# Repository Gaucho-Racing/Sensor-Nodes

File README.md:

# Sensor Node hardware and software for GR25

---

## Hardware 
The Hardware is split into a couple of folders and have Kicad projects that relate to the Sensor Nodes. This includes random projects and some hardware that might have been usefull.

---

## Software

Includes software for the Sensor Nodes

### Compilation:

To compile and be able to debug the project you need the following: 
- CMAKE 
- arm-none-eabi-gcc
- openocd
- ninja
- VSCode CMAKE extension
- VSCode Cortex Debug extension

**Make sure cmake, arm tolchian, openocd,and ninja are added to path**

To check the version run: 
- cmake --version
- arm-none-eabi-gcc --version
- openocd --version
- ninja --version

After everything is installed you should be able to follow the VSCode UI to compile and debug.

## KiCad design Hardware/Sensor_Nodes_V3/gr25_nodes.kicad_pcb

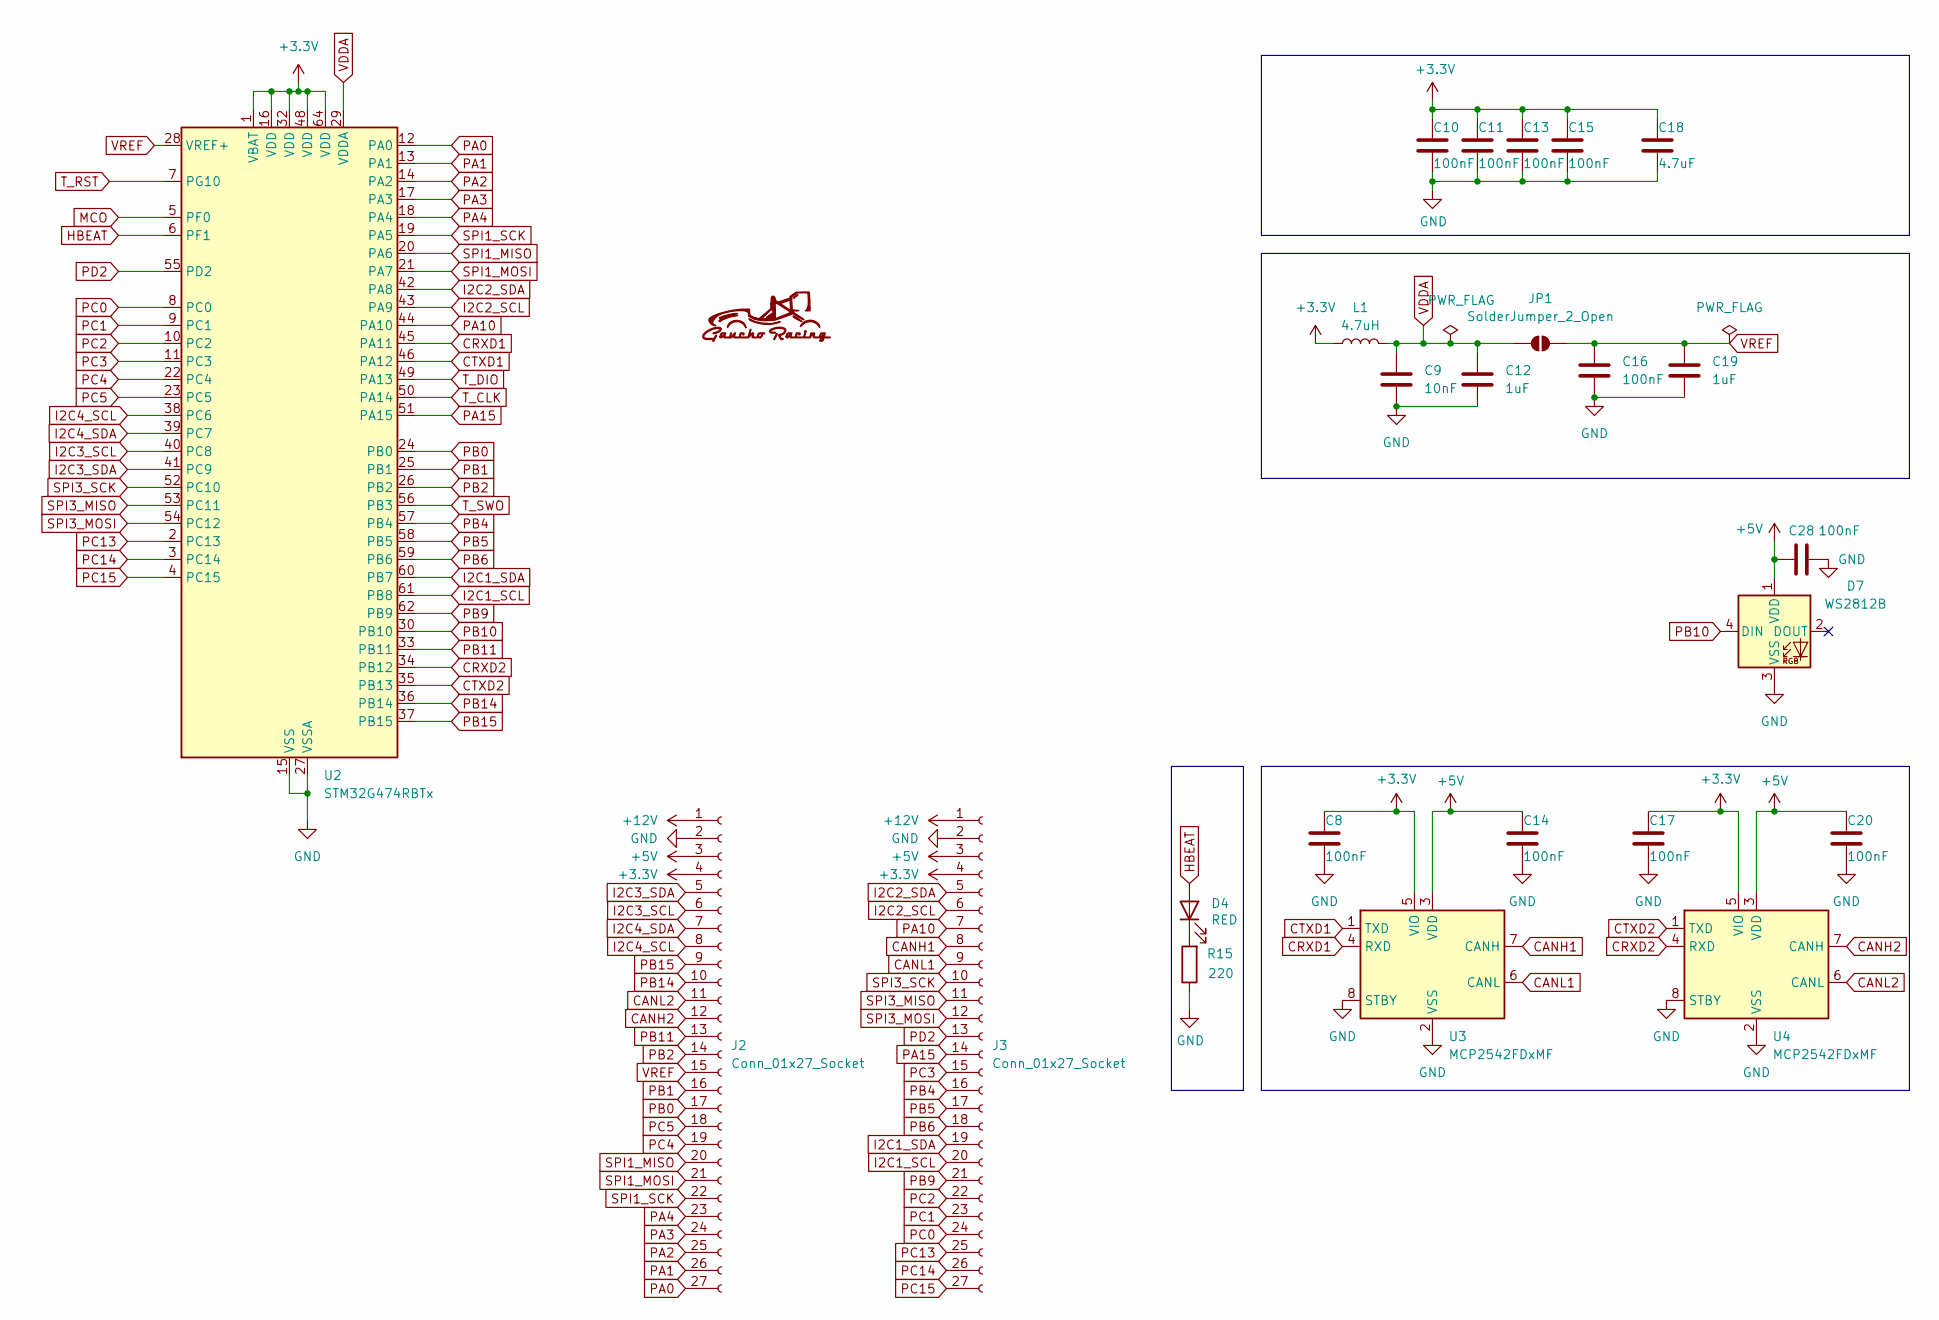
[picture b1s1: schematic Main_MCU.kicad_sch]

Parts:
C8, C10, C11, C13, C14, C15, C16, C17, C20: 100nF; C_0603_1608Metric; LCSC C14663
C9: 10nF; C_0603_1608Metric; LCSC C57112
C12, C19: 1uF; C_0603_1608Metric; LCSC C15849
C18: 4.7uF; C_0603_1608Metric; LCSC C19666
C28: 100nF; C_0603_1608Metric
D4: RED; LED_0603_1608Metric; LCSC C2286
D7: WS2812B; LED_WS2812B_PLCC4_5.0x5.0mm_P3.2mm
J2, J3: Conn_01x27_Socket; PinHeader_1x27_P2.54mm_Vertical
JP1: SolderJumper_2_Open; SolderJumper-2_P1.3mm_Open_TrianglePad1.0x1.5mm
L1: 4.7uH; C_1206_3216Metric; LCSC C1049
R15: 220; R_0402_1005Metric; LCSC C25091
U2: STM32G474RBTx; LQFP-64_10x10mm_P0.5mm; LCSC C529413
U3, U4: MCP2542FDxMF; SOIC-8_3.9x4.9mm_P1.27mm

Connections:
+3.3V: C8.1, C10.1, C11.1, C13.1, C15.1, C17.1, C18.1, J2.4, J3.4, L1.1, U2.1 (VBAT), U2.16 (VDD), U2.32 (VDD), U2.48 (VDD), U2.64 (VDD), U3.5 (VIO), U4.5 (VIO); also elsewhere on the board
+5V: C14.1, C20.1, C28.2, D7.1 (VDD), J2.3, J3.3, U3.3 (VDD), U4.3 (VDD); also elsewhere on the board
+12V: J2.1, J3.1; also elsewhere on the board
CANH1: J3.8, U3.7 (CANH)
CANH2: J2.12, U4.7 (CANH)
CANL1: J3.9, U3.6 (CANL)
CANL2: J2.11, U4.6 (CANL)
CRXD1: U2.45 (PA11), U3.4 (RXD)
CRXD2: U2.34 (PB12), U4.4 (RXD)
CTXD1: U2.46 (PA12), U3.1 (TXD)
CTXD2: U2.35 (PB13), U4.1 (TXD)
GND: C8.2, C9.2, C10.2, C11.2, C12.2, C13.2, C14.2, C15.2, C16.2, C17.2, C18.2, C19.2, C20.2, C28.1, D7.3 (VSS), J2.2, J3.2, R15.1, U2.15 (VSS), U2.27 (VSSA), U2.31 (VSS), U2.47 (VSS), U2.63 (VSS), U3.2 (VSS), U3.8 (STBY), U3.9 (VSS), U4.2 (VSS), U4.8 (STBY), U4.9 (VSS); also elsewhere on the board
HBEAT: D4.2 (A), U2.6 (PF1)
I2C1_SCL: J3.20, U2.61 (PB8)
I2C1_SDA: J3.19, U2.60 (PB7)
I2C2_SCL: J3.6, U2.43 (PA9)
I2C2_SDA: J3.5, U2.42 (PA8)
I2C3_SCL: J2.6, U2.40 (PC8)
I2C3_SDA: J2.5, U2.41 (PC9)
I2C4_SCL: J2.8, U2.38 (PC6)
I2C4_SDA: J2.7, U2.39 (PC7)
MCO: U2.5 (PF0); also elsewhere on the board
unnamed: D4.1 (K), R15.2
PA0: J2.27, U2.12 (PA0)
PA1: J2.26, U2.13 (PA1)
PA2: J2.25, U2.14 (PA2)
PA3: J2.24, U2.17 (PA3)
PA4: J2.23, U2.18 (PA4)
PA10: J3.7, U2.44 (PA10)
PA15: J3.14, U2.51 (PA15)
PB0: J2.17, U2.24 (PB0)
PB1: J2.16, U2.25 (PB1)
PB2: J2.14, U2.26 (PB2)
PB4: J3.16, U2.57 (PB4)
PB5: J3.17, U2.58 (PB5)
PB6: J3.18, U2.59 (PB6)
PB9: J3.21, U2.62 (PB9)
PB10: D7.4 (DIN), U2.30 (PB10)
PB11: J2.13, U2.33 (PB11)
PB14: J2.10, U2.36 (PB14)
PB15: J2.9, U2.37 (PB15)
PC0: J3.24, U2.8 (PC0)
PC1: J3.23, U2.9 (PC1)
PC2: J3.22, U2.10 (PC2)
PC3: J3.15, U2.11 (PC3)
PC4: J2.19, U2.22 (PC4)
PC5: J2.18, U2.23 (PC5)
PC13: J3.25, U2.2 (PC13)
PC14: J3.26, U2.3 (PC14)
PC15: J3.27, U2.4 (PC15)
PD2: J3.13, U2.55 (PD2)
SPI1_MISO: J2.20, U2.20 (PA6)
SPI1_MOSI: J2.21, U2.21 (PA7)
SPI1_SCK: J2.22, U2.19 (PA5)
SPI3_MISO: J3.11, U2.53 (PC11)
SPI3_MOSI: J3.12, U2.54 (PC12)
SPI3_SCK: J3.10, U2.52 (PC10)
T_CLK: U2.50 (PA14); also elsewhere on the board
T_DIO: U2.49 (PA13); also elsewhere on the board
T_RST: U2.7 (PG10); also elsewhere on the board
T_SWO: U2.56 (PB3); also elsewhere on the board
VDDA: C9.1, C12.1, JP1.1 (A), L1.2, U2.29 (VDDA)
VREF: C16.1, C19.1, J2.15, JP1.2 (B), U2.28 (VREF+)

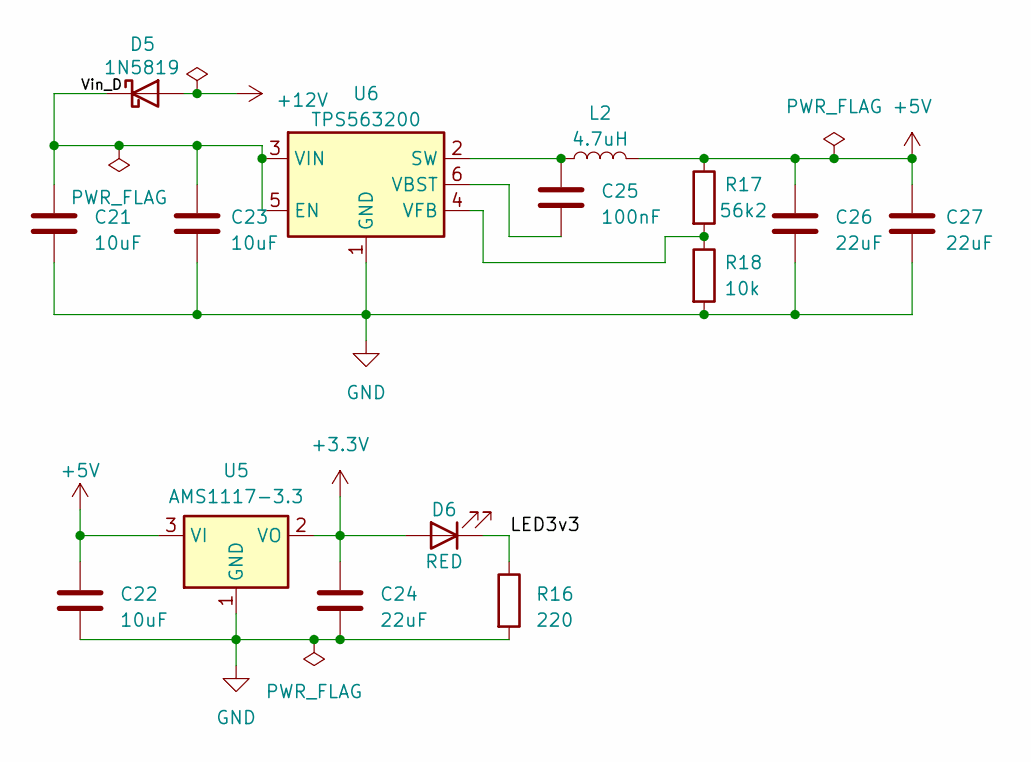
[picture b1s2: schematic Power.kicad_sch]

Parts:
C21, C22, C23: 10uF; C_0805_2012Metric; LCSC C15850
C24, C26, C27: 22uF; C_0805_2012Metric; LCSC C45783
C25: 100nF; C_0603_1608Metric; LCSC C14663
D5: 1N5819; D_SOD-323_HandSoldering; LCSC C191023
D6: RED; LED_0603_1608Metric; LCSC C2286
L2: 4.7uH; L_Cenker_CKCS6020; LCSC C5291878
R16: 220; R_0402_1005Metric; LCSC C25091
R17: 56k2; R_0402_1005Metric; LCSC C25796
R18: 10k; R_0402_1005Metric; LCSC C25744
U5: AMS1117-3.3; SOT-223-3_TabPin2; LCSC C6186
U6: TPS563200; SOT-23-6; LCSC C97253

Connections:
+3.3V: C24.1, D6.2 (A), U5.2 (VO); also elsewhere on the board
+5V: C22.1, C26.1, C27.1, L2.2, R17.1, U5.3 (VI); also elsewhere on the board
+12V: D5.2 (A); also elsewhere on the board
/Power/LED3v3: D6.1 (K), R16.1
/Power/Vin_D: C21.1, C23.1, D5.1 (K), U6.3 (VIN), U6.5 (EN)
GND: C21.2, C22.2, C23.2, C24.2, C26.2, C27.2, R16.2, R18.2, U5.1 (GND), U6.1 (GND); also elsewhere on the board
unnamed: C25.1, L2.1, U6.2 (SW)
unnamed: C25.2, U6.6 (VBST)
unnamed: R17.2, R18.1, U6.4 (VFB)

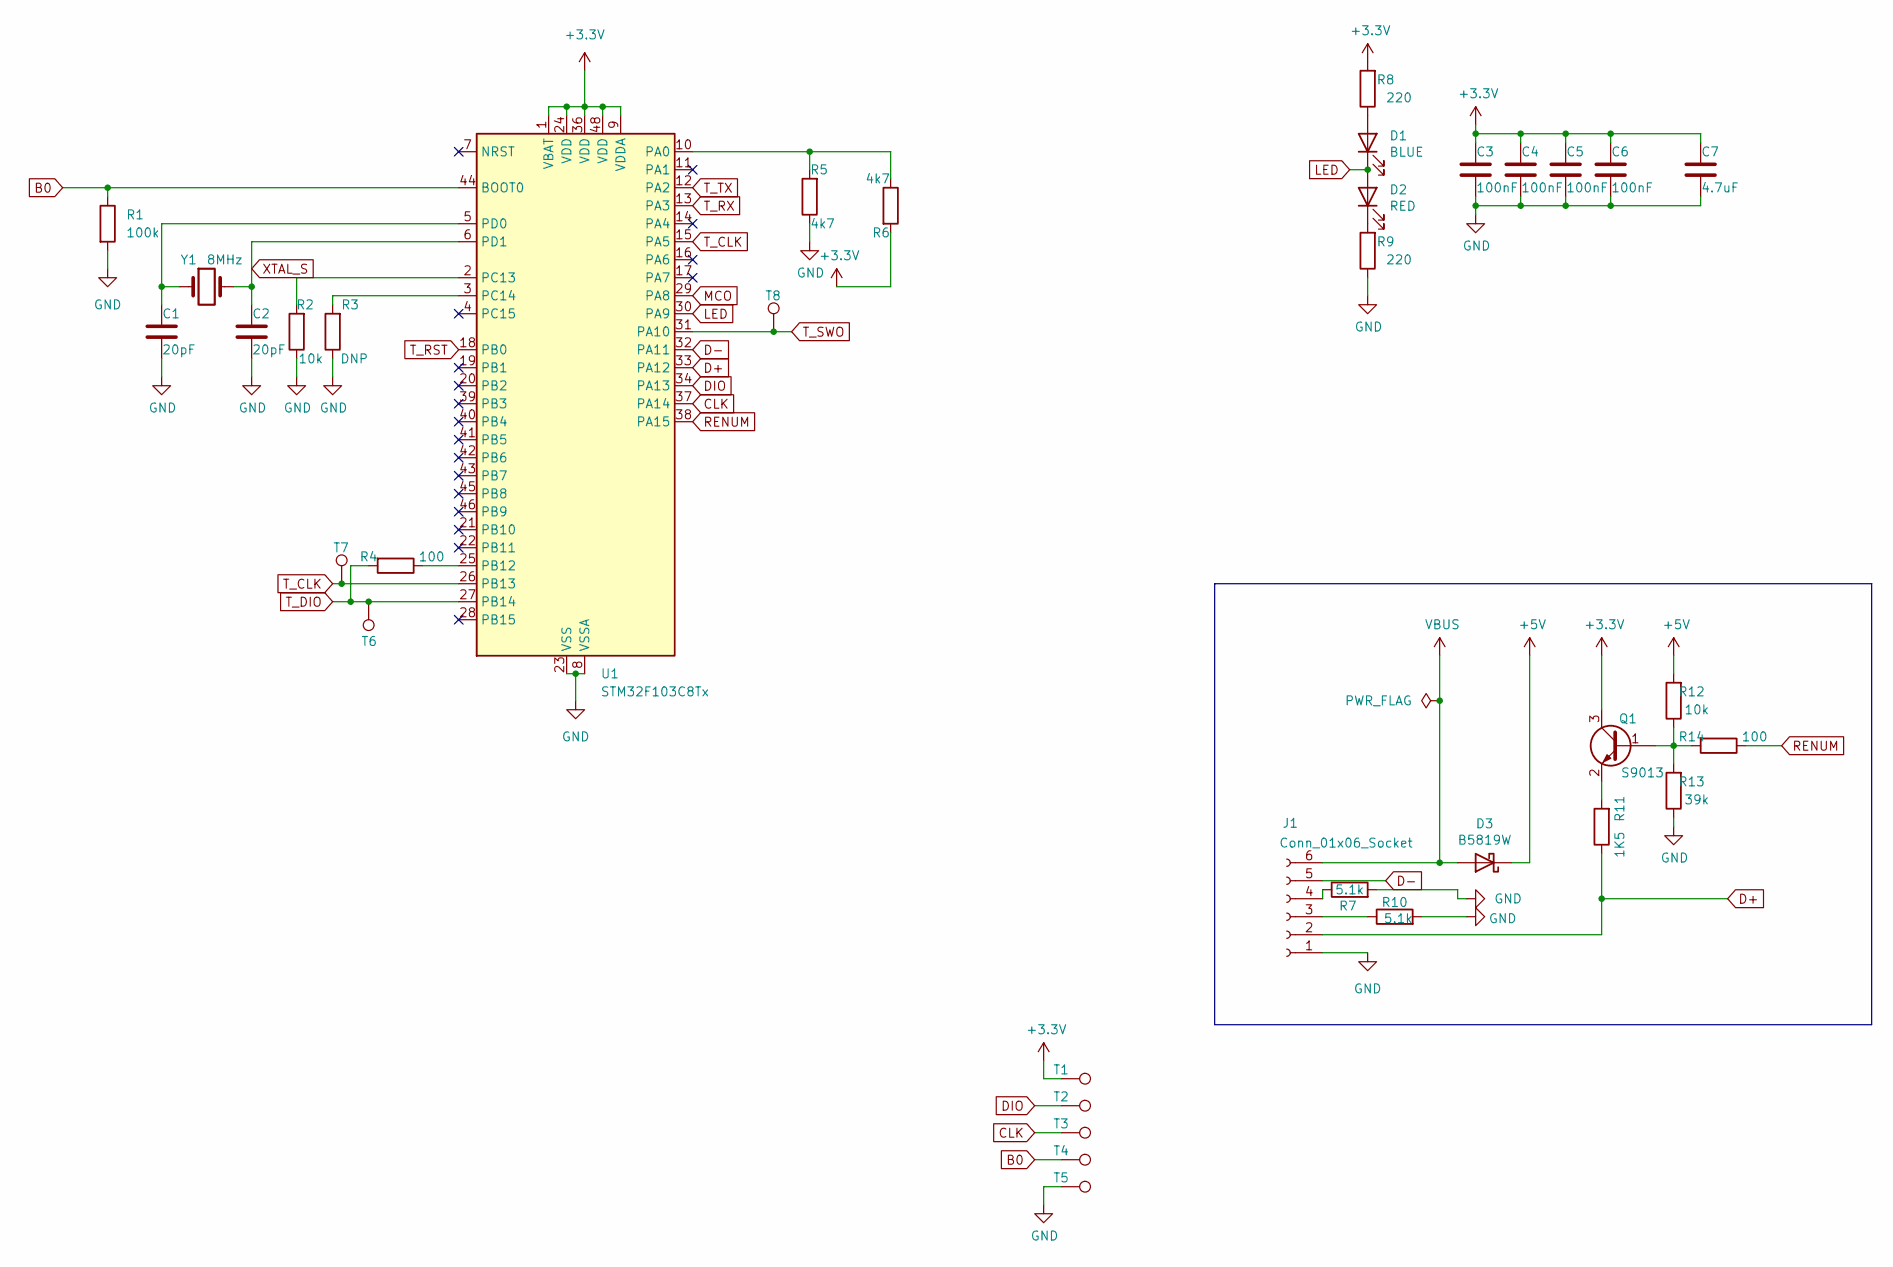
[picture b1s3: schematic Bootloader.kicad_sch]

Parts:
C1, C2: 20pF; C_0603_1608Metric; LCSC C1648
C3, C4, C5, C6: 100nF; C_0603_1608Metric; LCSC C14663
C7: 4.7uF; C_0603_1608Metric; LCSC C19666
D1: BLUE; LED_0603_1608Metric; LCSC C2290
D2: RED; LED_0603_1608Metric; LCSC C2286
D3: B5819W; D_SOD-123; LCSC C8598
J1: Conn_01x06_Socket; JST_PH_B6B-PH-K_1x06_P2.00mm_Vertical
Q1: S9013; SOT-23; LCSC C6749
R1: 100k; R_0402_1005Metric; LCSC C25741
R2, R12: 10k; R_0402_1005Metric; LCSC C25744
R3: DNP; R_0402_1005Metric; LCSC xxC25744
R4: 100; R_0603_1608Metric; LCSC C22775
R5, R6: 4k7; R_0402_1005Metric; LCSC C25900
R7, R10: 5.1k; R_0402_1005Metric; LCSC C25905
R8, R9: 220; R_0402_1005Metric; LCSC C25091
R11: 1K5; R_0402_1005Metric; LCSC C25867
R13: 39k; R_0402_1005Metric; LCSC C25783
R14: 100; R_0402_1005Metric; LCSC C25076
T1, T2, T3, T4, T5, T6, T7, T8: TestPoint_Pad_1.0x1.0mm
U1: STM32F103C8Tx; LQFP-48_7x7mm_P0.5mm; LCSC C8734
Y1: 8MHz; Crystal_SMD_5032-2Pin_5.0x3.2mm; LCSC C115962

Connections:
+3.3V: C3.1, C4.1, C5.1, C6.1, C7.1, Q1.3 (C), R6.2, R8.2, T1.1, U1.1 (VBAT), U1.9 (VDDA), U1.24 (VDD), U1.36 (VDD), U1.48 (VDD); also elsewhere on the board
+5V: D3.1 (K), R12.2; also elsewhere on the board
B0: R1.1, T4.1, U1.44 (BOOT0)
CLK: T3.1, U1.37 (PA14)
D+: J1.2, R11.1, U1.33 (PA12)
D-: J1.5, U1.32 (PA11)
DIO: T2.1, U1.34 (PA13)
GND: C1.2, C2.2, C3.2, C4.2, C5.2, C6.2, C7.2, J1.1, R1.2, R2.1, R3.1, R5.1, R7.2, R9.1, R10.2, R13.1, T5.1, U1.8 (VSSA), U1.23 (VSS), U1.35 (VSS), U1.47 (VSS); also elsewhere on the board
LED: D1.1 (K), D2.2 (A), U1.30 (PA9)
MCO: U1.29 (PA8); also elsewhere on the board
unnamed: D1.2 (A), R8.1
unnamed: D2.1 (K), R9.2
unnamed: J1.3, R10.1
unnamed: J1.4, R7.1
unnamed: Q1.1 (B), R12.1, R13.2, R14.2
unnamed: Q1.2 (E), R11.2
unnamed: R5.2, R6.1, U1.10 (PA0)
unnamed: R4.1, U1.25 (PB12)
unnamed: R2.2, U1.2 (PC13)
unnamed: R3.2, U1.3 (PC14)
unnamed: C1.1, U1.5 (PD0), Y1.1
RENUM: R14.1, U1.38 (PA15)
T_CLK: T7.1, U1.15 (PA5), U1.26 (PB13); also elsewhere on the board
T_DIO: R4.2, T6.1, U1.27 (PB14); also elsewhere on the board
T_RST: U1.18 (PB0); also elsewhere on the board
T_RX: U1.13 (PA3)
T_SWO: T8.1, U1.31 (PA10); also elsewhere on the board
T_TX: U1.12 (PA2)
VBUS: D3.2 (A), J1.6
XTAL_S: C2.1, U1.6 (PD1), Y1.2

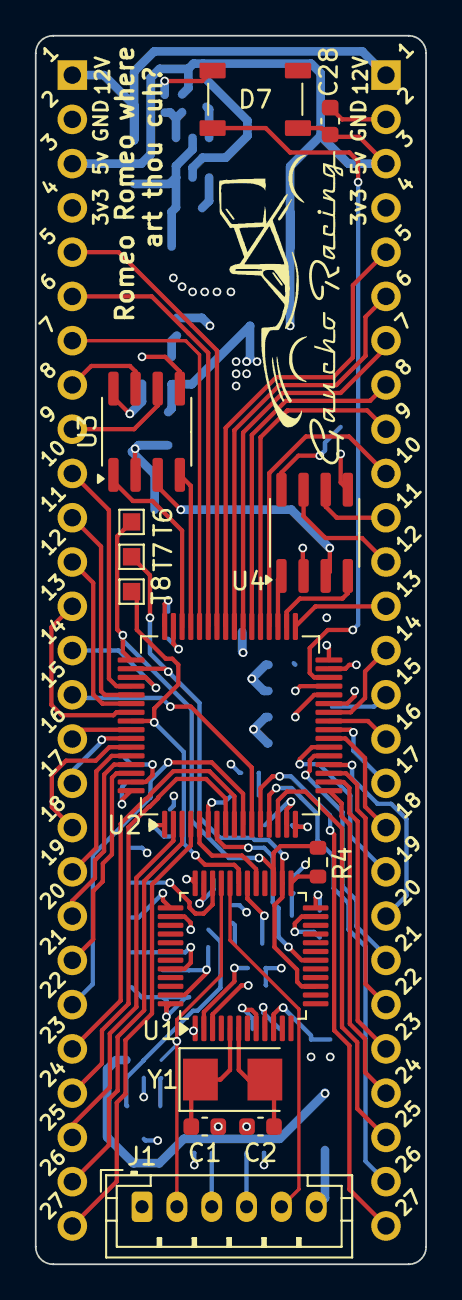
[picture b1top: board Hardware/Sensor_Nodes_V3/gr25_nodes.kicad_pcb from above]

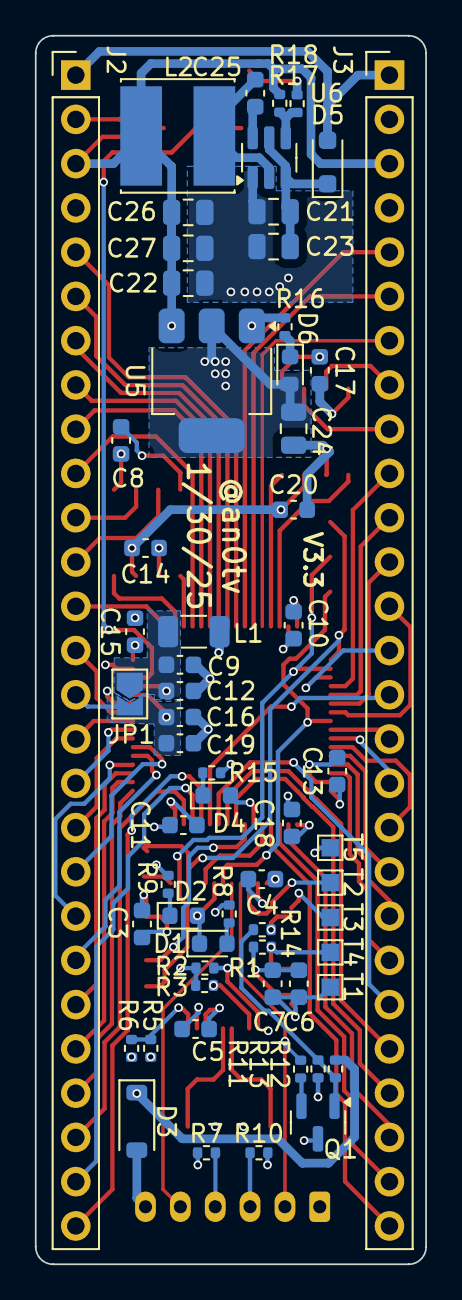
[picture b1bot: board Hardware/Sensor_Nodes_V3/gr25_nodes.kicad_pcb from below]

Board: 4 copper layers, 22.4 x 70.5 mm, 75 parts (61 on the bottom side), 88 nets.

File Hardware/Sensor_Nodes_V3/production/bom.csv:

Designator,Footprint,Quantity,Value,LCSC Part #
"_2, ",,2,,
"C1, C2",0603,2,20pF,C1648
"C10, C11, C13, C14, C15, C16, C17, C20, C25, C3, C4, C5, C6, C8",0603,14,100nF,C14663
"C12, C19",0603,2,1uF,C15849
"C18, C7",0603,2,4.7uF,C19666
"C21, C22, C23",0805,3,10uF, C15850
"C24, C26, C27",0805,3,22uF,C45783
C9,0603,1,10nF,C57112
D1,0603,1,BLUE, C2290
"D2, D4, D6",0603,3,RED,C2286
D3,D_SOD-123,1,B5819W,C8598
D5,D_SOD-323_HandSoldering,1,1N5819,C191023
J1,JST_PH_B6B-PH-K_1x06_P2.00mm_Vertical,1,Conn_01x06_Socket,
"J2, J3",PinHeader_1x27_P2.54mm_Vertical,2,Conn_01x27_Socket,
"KiKit_FID_B_1, KiKit_FID_B_2, KiKit_FID_B_3, KiKit_FID_T_1, KiKit_FID_T_2, KiKit_FID_T_3",Fiducial,6,Fiducial,
"KiKit_MB_1_1, KiKit_MB_1_2, KiKit_MB_1_3, KiKit_MB_1_4, KiKit_MB_1_5, KiKit_MB_2_1, KiKit_MB_2_2, KiKit_MB_2_3, KiKit_MB_2_4, KiKit_MB_2_5, KiKit_MB_3_1, KiKit_MB_3_2, KiKit_MB_3_3, KiKit_MB_3_4, KiKit_MB_3_5, KiKit_MB_4_1, KiKit_MB_4_2, KiKit_MB_4_3, KiKit_MB_4_4, KiKit_MB_4_5, KiKit_TO_1",NPTH,21,NPTH,
L1,1206,1,4.7uH,C1049
L2,L_Cenker_CKCS6020,1,4.7uH,C5291878
Q1,SOT-23,1,S9013,C6749
R1,0402,1,100k,C25741
"R10, R7",0402,2,5.1k,C25905
R11,0402,1,1K5,C25867
"R12, R18, R2",0402,3,10k,C25744
R13,0402,1,39k,C25783
R14,0402,1,100,C25076
"R15, R16, R8, R9",0402,4,220,C25091
R17,0402,1,56k2,C25796
R4,0603,1,100,C22775
"R5, R6",0402,2,4k7,C25900
"T1, T2, T3, T4, T5, T6, T7, T8",TestPoint_Pad_1.0x1.0mm,8,~,
U1,LQFP-48_7x7mm_P0.5mm,1,STM32F103C8Tx,C8734
U2,LQFP-64_10x10mm_P0.5mm,1,STM32G474RBTx,C529413
"U3, U4",SOIC-8_3.9x4.9mm_P1.27mm,2,MCP2542FDxMF,
U5,SOT-223-3_TabPin2,1,AMS1117-3.3,C6186
U6,SOT-23-6,1,TPS563200,C97253
Y1,Crystal_SMD_5032-2Pin_5.0x3.2mm,1,8MHz,C115962

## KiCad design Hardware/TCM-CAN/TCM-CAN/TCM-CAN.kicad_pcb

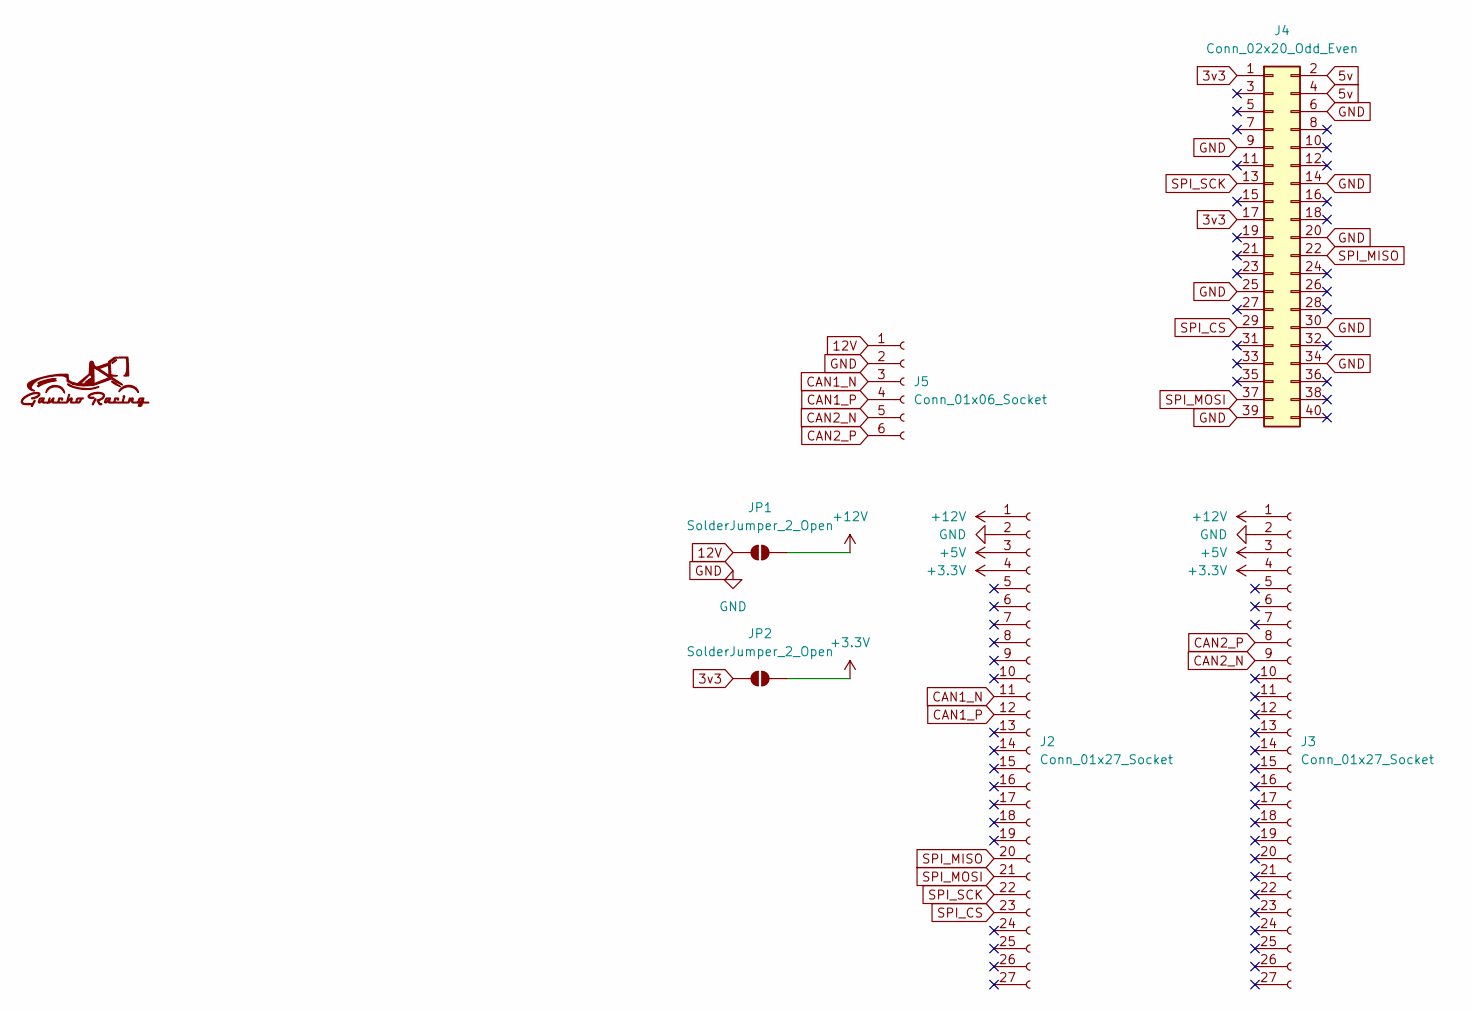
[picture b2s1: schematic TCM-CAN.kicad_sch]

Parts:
J2, J3: Conn_01x27_Socket; PinHeader_1x27_P2.54mm_Vertical
J4: Conn_02x20_Odd_Even; PinSocket_2x20_P2.54mm_Vertical
J5: Conn_01x06_Socket; JST_XH_B6B-XH-A_1x06_P2.50mm_Vertical
JP1, JP2: SolderJumper_2_Open; SolderJumper-2_P1.3mm_Open_Pad1.0x1.5mm

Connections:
3v3: J4.1, J4.17, JP2.1 (A)
5v: J4.2, J4.4
12V: J5.1, JP1.1 (A)
+3.3V: J2.4, J3.4, JP2.2 (B)
+5V: J2.3, J3.3
+12V: J2.1, J3.1, JP1.2 (B)
CAN1_N: J2.11, J5.3
CAN1_P: J2.12, J5.4
CAN2_N: J3.9, J5.5
CAN2_P: J3.8, J5.6
GND: J2.2, J3.2, J4.6, J4.9, J4.14, J4.20, J4.25, J4.30, J4.34, J4.39, J5.2
SPI_CS: J2.23, J4.29
SPI_MISO: J2.20, J4.22
SPI_MOSI: J2.21, J4.37
SPI_SCK: J2.22, J4.13

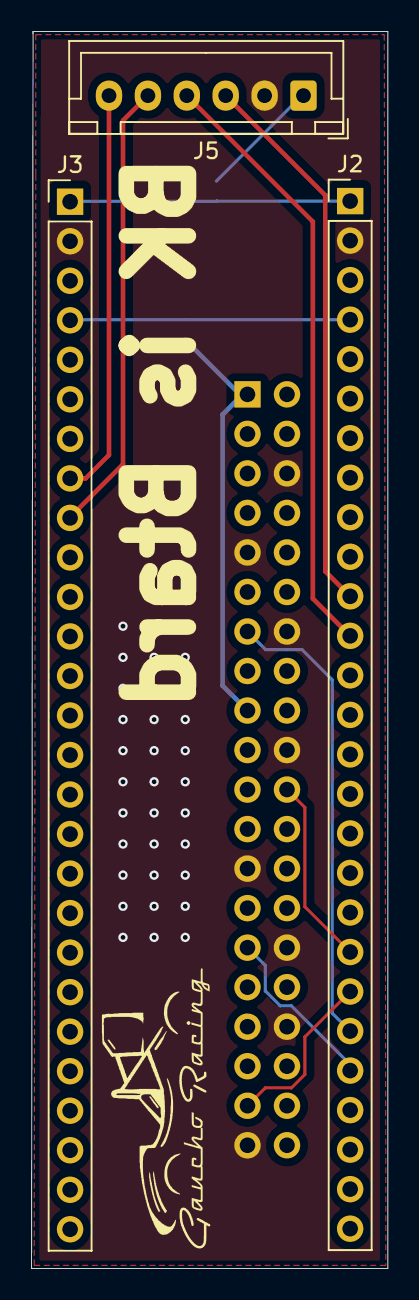
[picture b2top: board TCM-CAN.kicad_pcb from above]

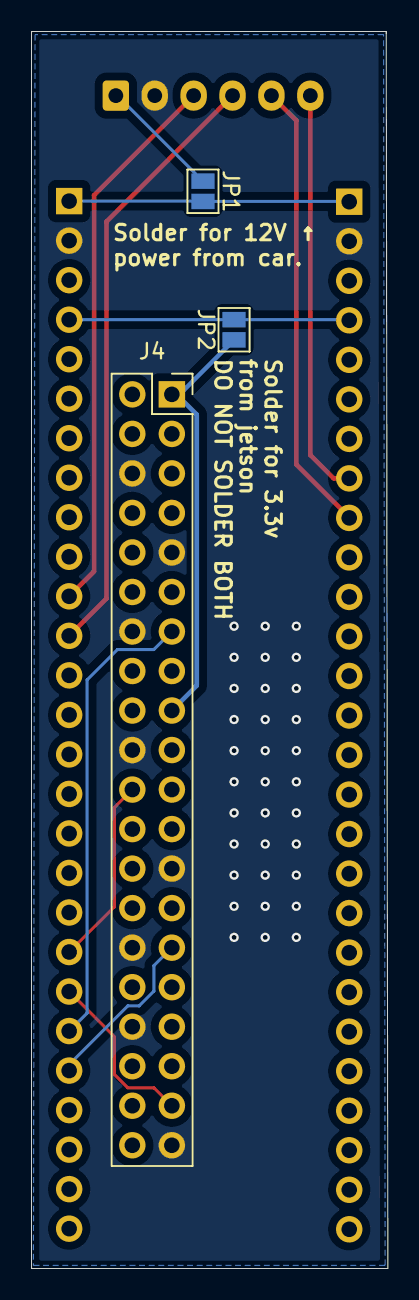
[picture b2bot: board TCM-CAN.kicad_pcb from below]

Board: 2 copper layers, 22.9 x 79.5 mm, 6 parts (3 on the bottom side), 15 nets.

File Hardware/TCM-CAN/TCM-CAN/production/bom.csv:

Designator,Footprint,Quantity,Value,LCSC Part #
"J2, J3",PinHeader_1x27_P2.54mm_Vertical,2,Conn_01x27_Socket,
J4,PinSocket_2x20_P2.54mm_Vertical,1,Conn_02x20_Odd_Even,
J5,JST_XH_B6B-XH-A_1x06_P2.50mm_Vertical,1,Conn_01x06_Socket,

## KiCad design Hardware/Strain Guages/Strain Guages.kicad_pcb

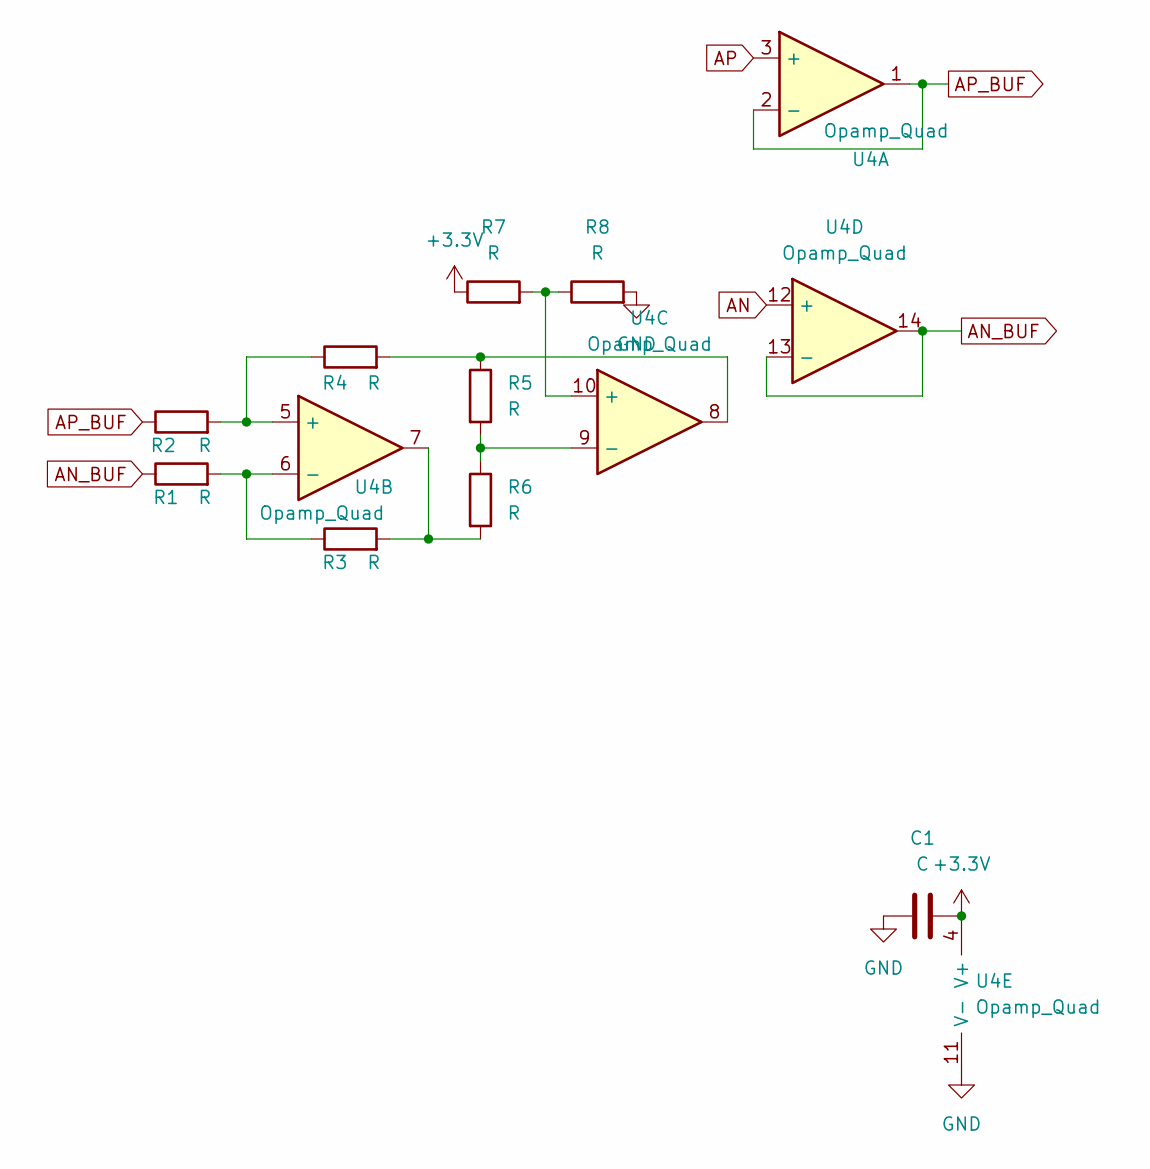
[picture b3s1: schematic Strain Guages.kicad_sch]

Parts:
C1: C; C_0603_1608Metric
R1, R2, R3, R4, R5, R6, R7, R8: R; R_0603_1608Metric
U4: Opamp_Quad; SOIC-14_3.9x8.7mm_P1.27mm

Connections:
+3.3V: C1.1, R7.1, U4.4 (V+)
AN: U4.12 (+)
AN_BUF: R1.1, U4.13 (-), U4.14
AP: U4.3 (+)
AP_BUF: R2.1, U4.1, U4.2 (-)
GND: C1.2, R8.2, U4.11 (V-)
unnamed: R3.2, R6.2, U4.7
unnamed: R4.2, R5.1, U4.8
unnamed: R2.2, R4.1, U4.5 (+)
unnamed: R1.2, R3.1, U4.6 (-)
unnamed: R7.2, R8.1, U4.10 (+)
unnamed: R5.2, R6.1, U4.9 (-)

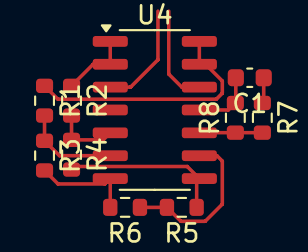
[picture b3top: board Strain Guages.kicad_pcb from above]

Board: 2 copper layers, 10 parts (0 on the bottom side), 10 nets.

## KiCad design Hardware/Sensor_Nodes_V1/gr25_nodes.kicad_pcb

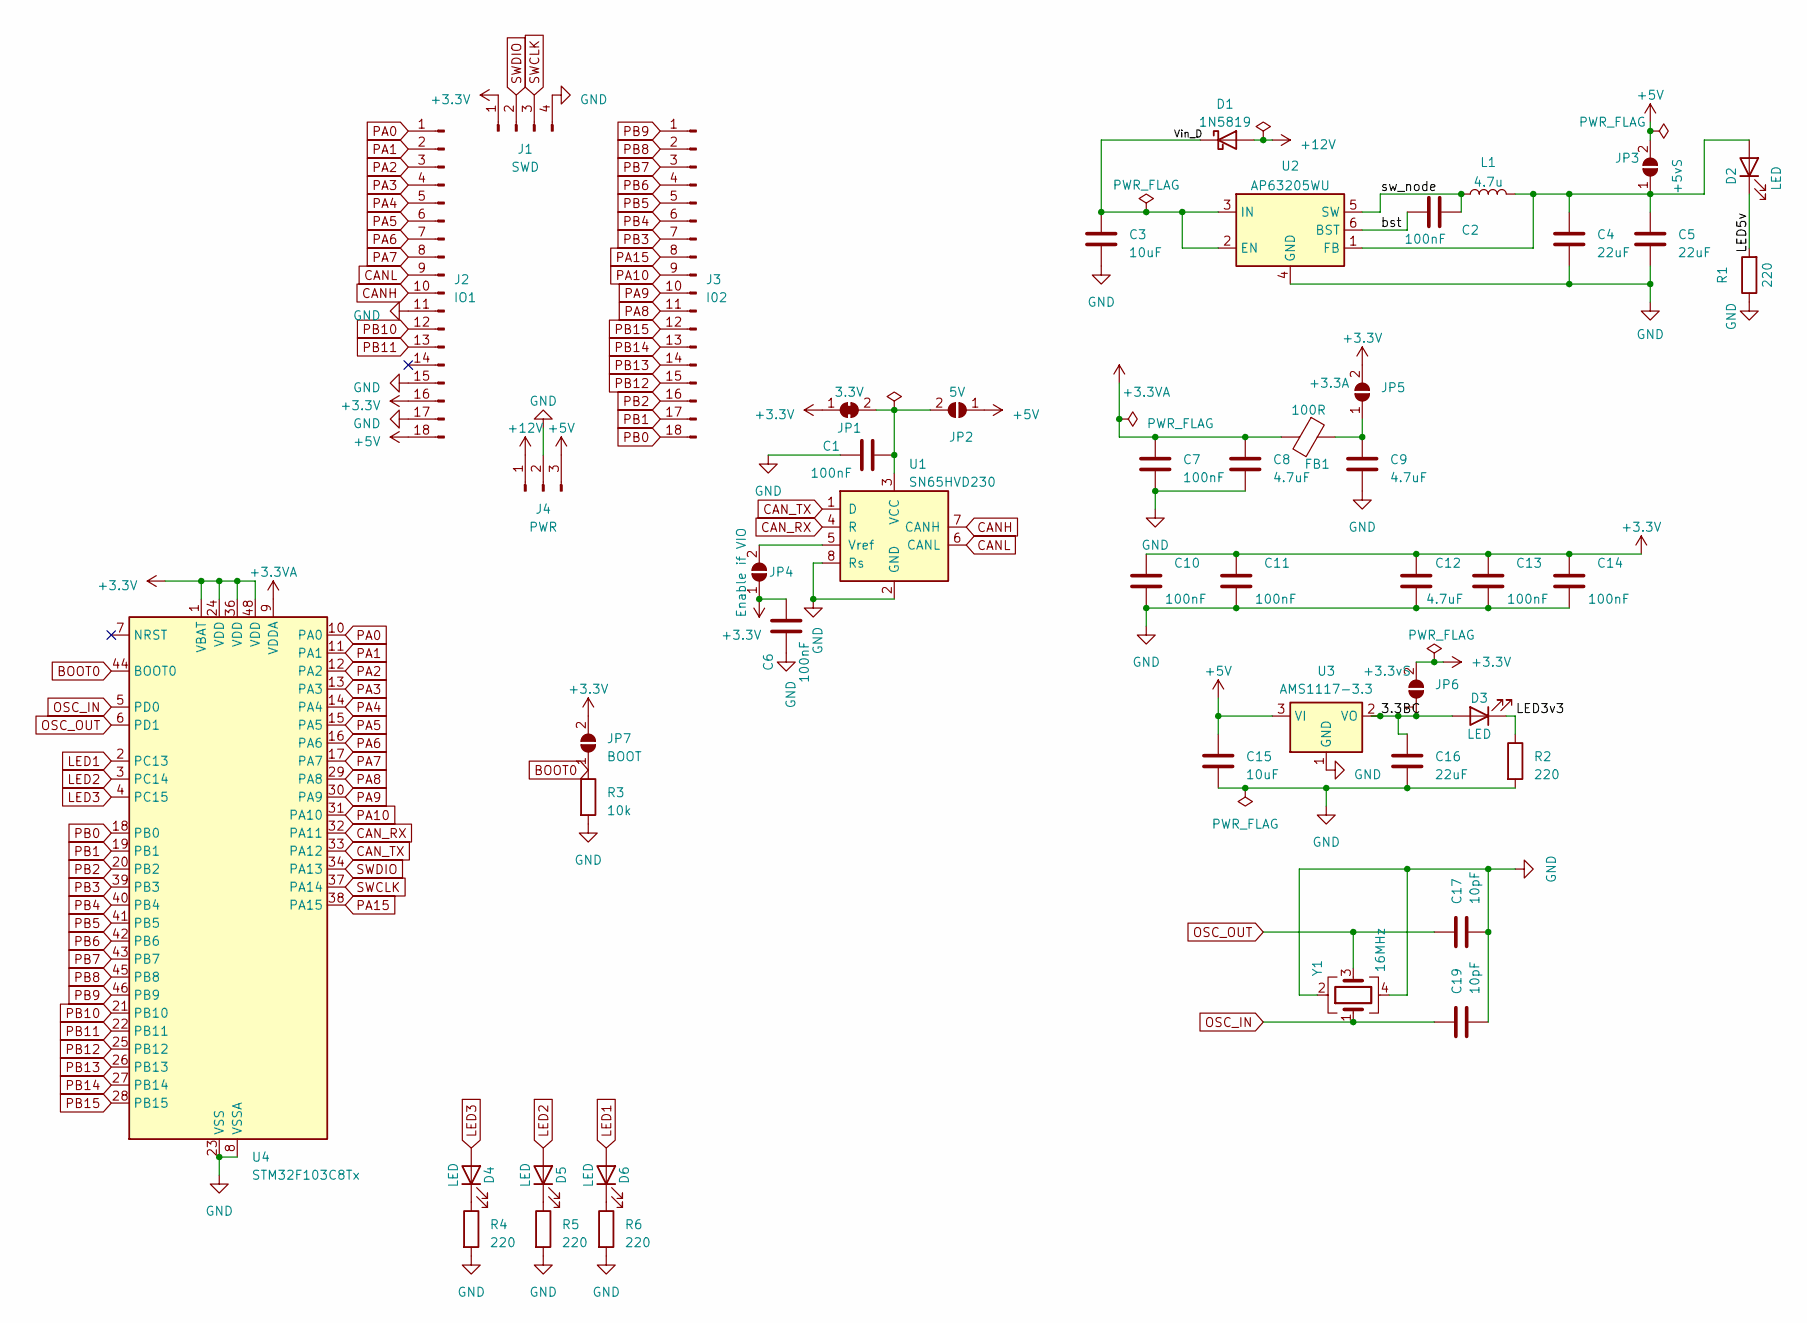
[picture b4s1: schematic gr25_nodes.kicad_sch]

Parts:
C1, C2, C6, C7, C10, C11, C13, C14: 100nF; C_0603_1608Metric; LCSC C14663
C3: 10uF; C_0805_2012Metric; LCSC C440198
C4, C5, C16: 22uF; C_1206_3216Metric; LCSC C12891
C8, C9, C12: 4.7uF; C_0603_1608Metric; LCSC C19666
C15: 10uF; C_0603_1608Metric; LCSC C96446
C17, C19: 10pF; C_0603_1608Metric; LCSC C1634
D1: 1N5819; D_SOD-323_HandSoldering; LCSC C191023
D2, D3, D4, D5, D6: LED; D_0603_1608Metric; LCSC C2286
FB1: 100R; L_0805_2012Metric; LCSC C1015
J1: SWD; PinHeader_1x04_P2.54mm_Vertical
J2: IO1; PinHeader_1x18_P2.54mm_Vertical
J3: I02; PinHeader_1x18_P2.54mm_Vertical
J4: PWR; PinHeader_1x03_P2.54mm_Vertical
JP1: 3.3V; SolderJumper-2_P1.3mm_Bridged_RoundedPad1.0x1.5mm
JP2: 5V; SolderJumper-2_P1.3mm_Open_RoundedPad1.0x1.5mm
JP3: +5vS; SolderJumper-2_P1.3mm_Open_RoundedPad1.0x1.5mm
JP4: Enable if VIO; SolderJumper-2_P1.3mm_Open_RoundedPad1.0x1.5mm
JP5: +3.3A; SolderJumper-2_P1.3mm_Open_RoundedPad1.0x1.5mm
JP6: +3.3vS; SolderJumper-2_P1.3mm_Open_RoundedPad1.0x1.5mm
JP7: BOOT; SolderJumper-2_P1.3mm_Open_RoundedPad1.0x1.5mm
L1: 4.7u; L_Bourns-SRN4018; PARTNUM SRN4018-4R7M
R1, R2, R4, R5, R6: 220; R_0603_1608Metric; LCSC C22962
R3: 10k; R_0603_1608Metric; LCSC C25804
U1: SN65HVD230; SOIC-8_3.9x4.9mm_P1.27mm; LCSC C12084
U2: AP63205WU; TSOT-23-6; PARTNUM AP63205WU
U3: AMS1117-3.3; SOT-223-3_TabPin2; LCSC C6186
U4: STM32F103C8Tx; LQFP-48_7x7mm_P0.5mm; LCSC C8734
Y1: 16MHz; Crystal_SMD_3225-4Pin_3.2x2.5mm; LCSC C13738

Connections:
+3.3V: C6.1, C10.1, C11.1, C12.1, C13.1, C14.1, J1.1, J2.16, JP1.1 (A), JP4.1 (A), JP5.2 (B), JP6.2 (B), JP7.2 (B), U4.1 (VBAT), U4.24 (VDD), U4.36 (VDD), U4.48 (VDD)
+3.3VA: C7.1, C8.1, FB1.2, U4.9 (VDDA)
+5V: C15.1, J2.18, J4.3, JP2.1 (A), JP3.2 (B), U3.3 (VI)
+12V: D1.2 (A), J4.1
/3.3BC: C16.1, D3.2 (A), JP6.1 (A), U3.2 (VO)
/LED3v3: D3.1 (K), R2.1
/LED5v: D2.1 (K), R1.2
/Vin_D: C3.1, D1.1 (K), U2.2 (EN), U2.3 (IN)
/bst: C2.1, U2.6 (BST)
/sw_node: C2.2, L1.1, U2.5 (SW)
BOOT0: JP7.1 (A), R3.1, U4.44 (BOOT0)
CANH: J2.10, U1.7 (CANH)
CANL: J2.9, U1.6 (CANL)
CAN_RX: U1.4 (R), U4.32 (PA11)
CAN_TX: U1.1 (D), U4.33 (PA12)
GND: C1.2, C3.2, C4.2, C5.2, C6.2, C7.2, C8.2, C9.2, C10.2, C11.2, C12.2, C13.2, C14.2, C15.2, C16.2, C17.2, C19.2, J1.4, J2.11, J2.15, J2.17, J4.2, R1.1, R2.2, R3.2, R4.2, R5.2, R6.2, U1.2 (GND), U1.8 (Rs), U2.4 (GND), U3.1 (GND), U4.8 (VSSA), U4.23 (VSS), U4.35 (VSS), U4.47 (VSS), Y1.2, Y1.4
LED1: D6.2 (A), U4.2 (PC13)
LED2: D5.2 (A), U4.3 (PC14)
LED3: D4.2 (A), U4.4 (PC15)
unnamed: C1.1, JP1.2 (B), JP2.2 (B), U1.3 (VCC)
unnamed: C4.1, C5.1, D2.2 (A), JP3.1 (A), L1.2, U2.1 (FB)
unnamed: D4.1 (K), R4.1
unnamed: D5.1 (K), R5.1
unnamed: D6.1 (K), R6.1
unnamed: JP4.2 (B), U1.5 (Vref)
unnamed: C9.1, FB1.1, JP5.1 (A)
OSC_IN: C19.1, U4.5 (PD0), Y1.1
OSC_OUT: C17.1, U4.6 (PD1), Y1.3
PA0: J2.1, U4.10 (PA0)
PA1: J2.2, U4.11 (PA1)
PA2: J2.3, U4.12 (PA2)
PA3: J2.4, U4.13 (PA3)
PA4: J2.5, U4.14 (PA4)
PA5: J2.6, U4.15 (PA5)
PA6: J2.7, U4.16 (PA6)
PA7: J2.8, U4.17 (PA7)
PA8: J3.11, U4.29 (PA8)
PA9: J3.10, U4.30 (PA9)
PA10: J3.9, U4.31 (PA10)
PA15: J3.8, U4.38 (PA15)
PB0: J3.18, U4.18 (PB0)
PB1: J3.17, U4.19 (PB1)
PB2: J3.16, U4.20 (PB2)
PB3: J3.7, U4.39 (PB3)
PB4: J3.6, U4.40 (PB4)
PB5: J3.5, U4.41 (PB5)
PB6: J3.4, U4.42 (PB6)
PB7: J3.3, U4.43 (PB7)
PB8: J3.2, U4.45 (PB8)
PB9: J3.1, U4.46 (PB9)
PB10: J2.12, U4.21 (PB10)
PB11: J2.13, U4.22 (PB11)
PB12: J3.15, U4.25 (PB12)
PB13: J3.14, U4.26 (PB13)
PB14: J3.13, U4.27 (PB14)
PB15: J3.12, U4.28 (PB15)
SWCLK: J1.3, U4.37 (PA14)
SWDIO: J1.2, U4.34 (PA13)

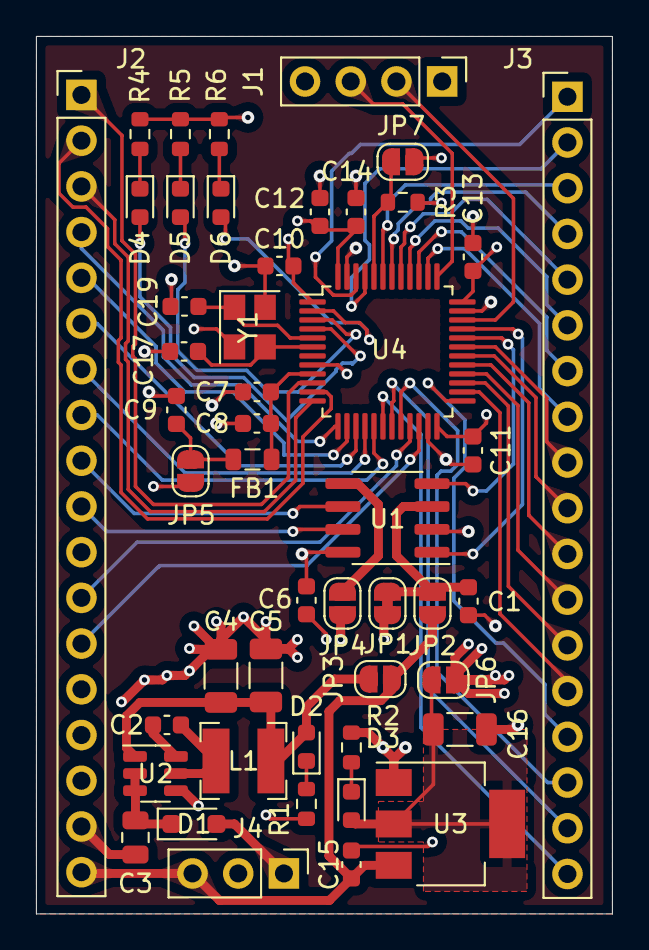
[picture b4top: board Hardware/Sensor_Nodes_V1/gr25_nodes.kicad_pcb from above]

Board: 4 copper layers, 32.0 x 48.8 mm, 48 parts (0 on the bottom side), 58 nets.
